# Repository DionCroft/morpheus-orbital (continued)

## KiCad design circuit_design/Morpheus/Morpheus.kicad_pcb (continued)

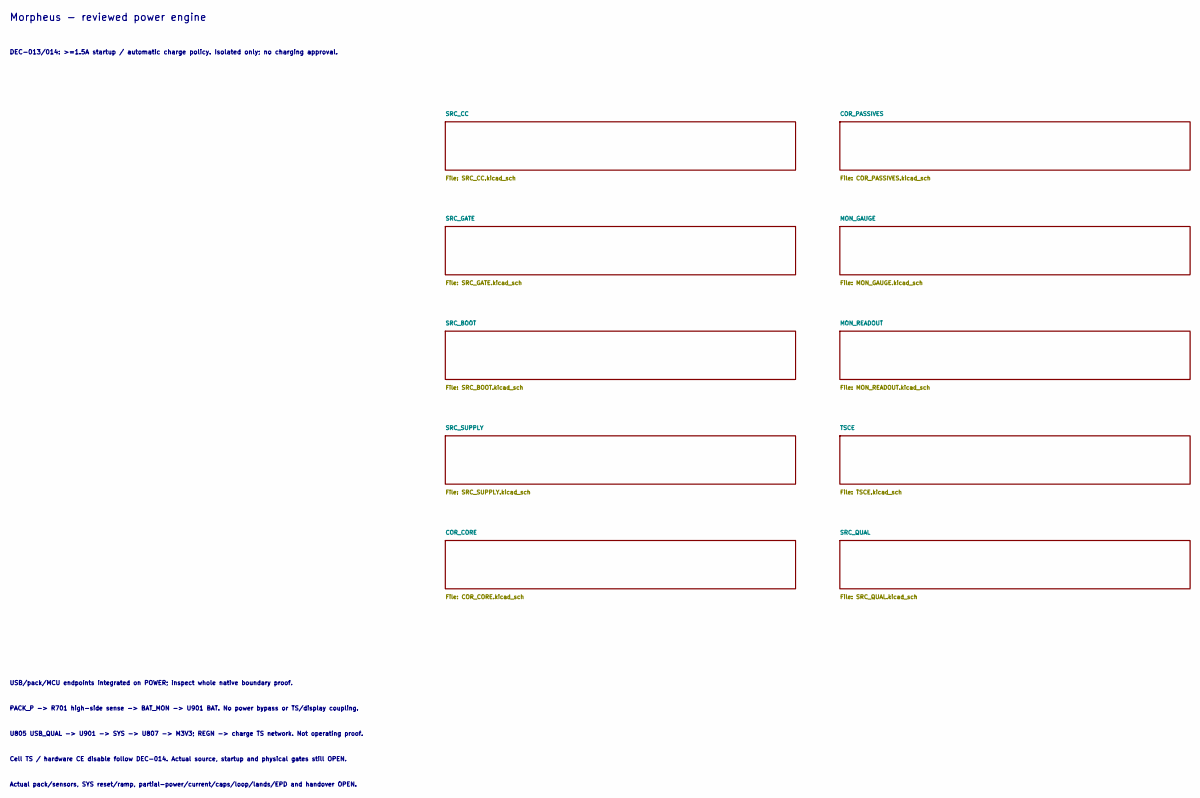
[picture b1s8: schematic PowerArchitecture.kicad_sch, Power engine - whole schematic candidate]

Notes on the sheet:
Morpheus - reviewed power engine
DEC-013/014: >=1.5A startup / automatic charge policy. Isolated only; no charging approval.
USB/pack/MCU endpoints integrated on POWER; inspect whole native boundary proof.
PACK_P -> R701 high-side sense -> BAT_MON -> U901 BAT. No power bypass or TS/display coupling.
U805 USB_QUAL -> U901 -> SYS -> U807 -> M3V3; REGN -> charge TS network. Not operating proof.
Cell TS / hardware CE disable follow DEC-014. Actual source, startup and physical gates still OPEN.
Actual pack/sensors, SYS reset/ramp, partial-power/current/caps/loop/lands/EPD and handover OPEN.

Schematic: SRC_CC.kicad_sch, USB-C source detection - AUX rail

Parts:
C801: 1u/50V; Samsung_C0805; ManufacturerPartNumber CL21B105KBFNNNE
C802: 4.7u/50V; Samsung_C1206; ManufacturerPartNumber CL31B475KBHNNNE
C803: 100n/50V; Samsung_C0603; ManufacturerPartNumber CL10B104KB8NNNC
R801: 0R - direct VBUS sense; R_0603_1608Metric; ManufacturerPartNumber RC0603JR-070RL
R802: 10k 1%; R_0603_1608Metric; ManufacturerPartNumber RC0603FR-0710KL
R812: 220R 1% 0.25W 1206; R_1206_3216Metric; ManufacturerPartNumber RC1206FR-07220RL
U801: TPS70933DBVR - AUX; TI_DBV0005A; ManufacturerPartNumber TPS70933DBVR
U802: FUSB303B - GPIO sink; Onsemi_722AG; ManufacturerPartNumber FUSB303BTMX

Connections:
C_ADVERT_N: R802.2, U802.7 (OUT1_ADVERT_N); also elsewhere on the board
C_AUDIO_OK: U802.6 (OUT3_AUDIO_N); also elsewhere on the board
C_AUX_IN: C801.1, R812.2, U801.1 (IN)
C_CC1: U802.1 (CC1); also elsewhere on the board
C_CC2: U802.2 (CC2); also elsewhere on the board
C_CC3V3: C802.1, C803.1, R802.1, U801.5 (OUT), U802.12 (VDD); also elsewhere on the board
C_PORT_DEBUG_N: U802.3 (PORT_DEBUG_N); also elsewhere on the board
C_SINK_OK: U802.9 (ID_SINK_OK); also elsewhere on the board
C_USB_RAW: R801.1, R812.1; also elsewhere on the board
C_VB_SENSE: R801.2, U802.4 (VBUS_DET)
GND: C801.2, C802.2, C803.2, U801.2 (GND), U802.10 (GND), U802.11 (EN_N); also elsewhere on the board

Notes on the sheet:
USB-C source detection - AUX rail
ISOLATED FUNCTIONAL CANDIDATE - primary conditions / actual integration / physical gates OPEN
FUSB PORT has10k sink strap, then DEBUG_N output; ADDR open selects GPIO.
R8010R connects FUSB VBUS_DET directly; old TUSB900k divider is NOT compatible.
R812220R limits AUX branch under stated5.5V/R/temperature conditions. Startup/lands OPEN.

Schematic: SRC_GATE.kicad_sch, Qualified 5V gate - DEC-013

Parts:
C804, C805: 100n/50V; Samsung_C0603; ManufacturerPartNumber CL10B104KB8NNNC
C806: 1u/50V; Samsung_C0805; ManufacturerPartNumber CL21B105KBFNNNE
C807: 10u/50V; Samsung_C1210; ManufacturerPartNumber CL32B106KBJNNNE
C816: 220n/50V; Samsung_C0805; ManufacturerPartNumber CL21B224KBFNNNE
R804: 300k 1%; R_0603_1608Metric; ManufacturerPartNumber RC0603FR-07300KL
R805: 249k 1%; R_0603_1608Metric; ManufacturerPartNumber RC0603FR-07249KL
R806: 22k 1%; R_0603_1608Metric; ManufacturerPartNumber RC0603FR-0722KL
U803: SN74LVC1G14DBVR; TI_DBV0005A; ManufacturerPartNumber SN74LVC1G14DBVR
U804: TPS389030DSET; TI_DSE0006A; ManufacturerPartNumber TPS389030DSET
U805: TPS2553DBVR; TI_DBV0006A; ManufacturerPartNumber TPS2553DBVR

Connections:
C_ADVERT_N: U803.2 (A); also elsewhere on the board
C_ADVERT_OK: U803.4 (Y); also elsewhere on the board
C_CC3V3: C804.1, C805.1, U803.5 (VCC), U804.1 (SENSE), U804.3 (MR_N), U804.4 (VDD); also elsewhere on the board
C_CC_CT: C816.1, U804.5 (CT)
C_DRV: R804.1; also elsewhere on the board
C_SRC_ILIM: R806.1, U805.5 (ILIM)
C_SW_ENABLE: R804.2, R805.1, U804.6 (RESET_N), U805.3 (EN)
C_USB_QUAL: C807.1, U805.6 (OUT); also elsewhere on the board
C_USB_RAW: C806.1, U805.1 (IN); also elsewhere on the board
GND: C804.2, C805.2, C806.2, C807.2, C816.2, R805.2, R806.2, U803.3 (GND), U804.2 (GND), U805.2 (GND); also elsewhere on the board

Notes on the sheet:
Qualified 5V gate - DEC-013
ISOLATED FUNCTIONAL CANDIDATE - primary conditions / actual integration / physical gates OPEN
TPS3890 RESET6 clamps EN; MR3 tied VDD4. Numerical map is NOT TPS3808-compatible.
R80622k + separate AUX220R: conditional DC budget only; ramp/transient/compliance OPEN.
C816220nF CT5-to-GND gives nominal235ms only; effectiveC/leakage/dynamic proof held.

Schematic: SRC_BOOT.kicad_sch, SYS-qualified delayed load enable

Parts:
C808, C811: 100n/50V; Samsung_C0603; ManufacturerPartNumber CL10B104KB8NNNC
C809, C810: 10u/50V; Samsung_C1210; ManufacturerPartNumber CL32B106KBJNNNE
C817: 220n/50V; Samsung_C0805; ManufacturerPartNumber CL21B224KBFNNNE
R808: 470k 1%; R_0603_1608Metric; ManufacturerPartNumber RC0603FR-07470KL
R809: 1M 1%; R_0603_1608Metric; ManufacturerPartNumber RC0603FR-071ML
U806: TPS389030DSET; TI_DSE0006A; ManufacturerPartNumber TPS389030DSET
U807: TPS63020DSJR; TI_DSJ14_PAD; ManufacturerPartNumber TPS63020DSJR

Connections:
3V3: U807.4 (VOUT4), U807.5 (VOUT5); also elsewhere on the board
C_BOOT_EN: R808.2, R809.1, U806.6 (RESET_N), U807.12 (EN)
C_FB: U807.3 (FB); also elsewhere on the board
C_L1: U807.8 (L1_8), U807.9 (L1_9); also elsewhere on the board
C_L2: U807.6 (L2_6), U807.7 (L2_7); also elsewhere on the board
C_SYS: C808.1, C809.1, C810.1, C811.1, R808.1, U806.1 (SENSE), U806.3 (MR_N), U806.4 (VDD), U807.1 (VINA), U807.10 (VIN10), U807.11 (VIN11); also elsewhere on the board
C_SYS_CT: C817.1, U806.5 (CT)
GND: C808.2, C809.2, C810.2, C811.2, C817.2, R809.2, U806.2 (GND), U807.2 (GND), U807.13 (PS_SYNC), U807.PAD (PGND_PAD_SWID); also elsewhere on the board

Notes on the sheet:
SYS-qualified delayed load enable
ISOLATED FUNCTIONAL CANDIDATE - primary conditions / actual integration / physical gates OPEN
TPS389030 rising2.907V nominal; R808470k bounds RESET load. CT220nF delay is nominal only.
U806 RESET6/MR3/VDD4/SENSE1; TPS63020 UVLO covers below POR. Actual load/transients OPEN.
PAD is an explicitly software-only thermal identifier. PS LOW enables low-load power save.

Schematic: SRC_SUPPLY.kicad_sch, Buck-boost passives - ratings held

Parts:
C812, C813, C814: 22u/25V; Samsung_C1210; ManufacturerPartNumber CL32B226KAJNNNE
L801: 1.5uH - current / lands HELD; Coilcraft_XGL4020; ManufacturerPartNumber XGL4020-152MEC
R810: 1M 0.1%; R_0603_1608Metric; ManufacturerPartNumber RT0603BRD071ML
R811: 180k 0.1%; Panasonic_ERA3A; ManufacturerPartNumber ERA3AEB184V

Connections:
3V3: C812.1, C813.1, C814.1, R810.1; also elsewhere on the board
C_FB: R810.2, R811.1; also elsewhere on the board
C_L1: L801.1; also elsewhere on the board
C_L2: L801.2; also elsewhere on the board
GND: C812.2, C813.2, C814.2, R811.2; also elsewhere on the board

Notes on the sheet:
Buck-boost passives - ratings held
ISOLATED FUNCTIONAL CANDIDATE - primary conditions / actual integration / physical gates OPEN
L8011.5uH +3x22uF follows documented nominal matrix; effective capacitance/inductor current still OPEN.
TI p15:1M/180k0.1% sets3.278V nominal; ripple/thermal/PCB gates OPEN.
Steady bounds include FB/PFM/line/load; they are NOT startup/load-step/fault guarantees.

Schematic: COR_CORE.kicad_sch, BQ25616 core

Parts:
U901: BQ25616RTWR NON-J; TI_RTW24_PAD; ManufacturerPartNumber BQ25616RTWR

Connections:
C_AGND: U901.6 (OTG); also elsewhere on the board
C_BAT_MON: U901.13 (BAT13), U901.14 (BAT14); also elsewhere on the board
C_BTST: U901.21 (BTST); also elsewhere on the board
C_CE9_N: U901.9 (CE_N); also elsewhere on the board
C_ICHG: U901.10 (ICHG); also elsewhere on the board
C_ILIM: U901.8 (ILIM); also elsewhere on the board
C_PG_N: U901.7 (PG_N); also elsewhere on the board
C_PMID: U901.23 (PMID); also elsewhere on the board
C_REGN: U901.22 (REGN); also elsewhere on the board
C_STAT_N: U901.5 (STAT_N); also elsewhere on the board
C_SW: U901.19 (SW19), U901.20 (SW20); also elsewhere on the board
C_SYS: U901.15 (SYS15), U901.16 (SYS16); also elsewhere on the board
C_TS11: U901.11 (TS); also elsewhere on the board
C_USB_QUAL: U901.1 (VAC), U901.24 (VBUS); also elsewhere on the board
C_VSET: U901.12 (VSET); also elsewhere on the board
GND: U901.17 (GND17), U901.18 (GND18), U901.PAD (PGND_SWID); also elsewhere on the board

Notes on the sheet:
BQ25616 non-J power-path functions
FUNCTIONAL CANDIDATE ONLY - source / permission / actual cell / lands / operating gates OPEN
VAC1=VBUS24, ACDRV2 open: manufacturer no-external-OVP option, NOT surge immunity.
BAT13/14 both charge and discharge through internal BATFET. SYS15/16 is NOT5V.
BTST21 consumes bootstrap supply; PMID23 supplies switching stage; SW19/20 drives L901.
D+3/D-4 NC: no charger loading on ESP32 USB. OTG6 LOW prevents intentional boost mode.
CE9/TS11 connect TSCE: autonomous cell sensing / manual disable; source and physical gates OPEN.
PAD is an unnumbered manufacturer thermal contact using an explicit software identifier.

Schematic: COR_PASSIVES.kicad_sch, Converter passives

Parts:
C90: 1n/50V C0G; Murata_GRM155_1nF_C0G_0402; ManufacturerPartNumber GRM1555C1H102JA01D
C901: 1u/50V; Samsung_C0805; ManufacturerPartNumber CL21B105KBFNNNE
C902, C905, C906, C907, C908: 10u/50V; Samsung_C1210; ManufacturerPartNumber CL32B106KBJNNNE
C903: 4.7u/50V; Samsung_C1206; ManufacturerPartNumber CL31B475KBHNNNE
C904: 47n/50V; Samsung_C0603; ManufacturerPartNumber CL10B473KB8NNNC
L901: 1uH - ratings / lands OPEN; Coilcraft_XAL5030; ManufacturerPartNumber XAL5030-102MEC
NT901: AGND STAR; AGND_Star_Thermal
R901: 1.5k 1% - ICHG; R_0603_1608Metric; ManufacturerPartNumber RC0603FR-071K5L
R902: 10k 1% - VSET; R_0603_1608Metric; ManufacturerPartNumber RC0603FR-0710KL
R903: 510R 1% - ILIM; R_0603_1608Metric; ManufacturerPartNumber RC0603FR-07510RL

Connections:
C_AGND: C903.2, NT901.1, R901.2, R902.2, R903.2; also elsewhere on the board
C_BAT_MON: C905.1; also elsewhere on the board
C_BTST: C904.1; also elsewhere on the board
C_ICHG: R901.1; also elsewhere on the board
C_ILIM: R903.1; also elsewhere on the board
C_PMID: C90.1, C902.1; also elsewhere on the board
C_REGN: C903.1; also elsewhere on the board
C_SW: C904.2, L901.1; also elsewhere on the board
C_SYS: C906.1, C907.1, C908.1, L901.2; also elsewhere on the board
C_USB_QUAL: C901.1; also elsewhere on the board
C_VSET: R902.1; also elsewhere on the board
GND: C90.2, C901.2, C902.2, C905.2, C906.2, C907.2, C908.2, NT901.2; also elsewhere on the board

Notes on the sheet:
Converter passives - effective C / current held
FUNCTIONAL CANDIDATE ONLY - source / permission / actual cell / lands / operating gates OPEN
C904 spans BTST-SW, never BTST-GND. L901 spans SW-SYS, not BAT-SYS.
Three nominal10uF SYS parts do NOT prove effectiveC>10uF / loop / ripple / thermal.
R9011.5k: conditional639..715/R at primary rows; actual cell/current acceptance OPEN.
R90210k selects4.1V non-J; R903510R only unknown-source ILIM, NOT universal clamp.
Exact MPNs/lands reviewed; effective C, dynamic current and assembly qualification remain held.

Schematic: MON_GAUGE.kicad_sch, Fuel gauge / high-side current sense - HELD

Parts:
C701: 1u/50V; Samsung_C0805; ManufacturerPartNumber CL21B105KBFNNNE
C702: 470n/50V; Samsung_C0805; ManufacturerPartNumber CL21B474KBFNNNE
R701: 10m 1% 1W 50ppm/K; Bourns_CRF1206; ManufacturerPartNumber CRF1206-FZ-R010ELF
R702, R703: 10k 1%; R_0603_1608Metric; ManufacturerPartNumber RC0603FR-0710KL
R704, R705: 1M 1%; R_0603_1608Metric; ManufacturerPartNumber RC0603FR-071ML
U701: BQ27441DRZR-G1A; TI_DRZ0012A; ManufacturerPartNumber BQ27441DRZR-G1A

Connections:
3V3: R703.1; also elsewhere on the board
C_BAT_MON: R701.2, U701.7 (SRN); also elsewhere on the board
C_BIN: R702.1, U701.10 (BIN)
C_GAUGE1V8: C702.1, U701.5 (VDD_1V8)
C_PACK_P: C701.1, R701.1, U701.6 (BAT_KELVIN), U701.8 (SRP); also elsewhere on the board
FUEL_GAUGE_INT: R703.2, U701.12 (GPOUT); also elsewhere on the board
GND: C701.2, C702.2, R702.2, R704.2, R705.2, U701.3 (VSS), U701.13 (PWPD_FIG6); also elsewhere on the board
I2C_SCL: R705.1, U701.2 (SCL); also elsewhere on the board
I2C_SDA: R704.1, U701.1 (SDA); also elsewhere on the board

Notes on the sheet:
Morpheus - Fuel gauge / high-side current sense - HELD
INTEGRATED FUNCTION CANDIDATE - reset/current/physical qualification OPEN; no charge release
PACK_P is Kelvin cell-positive; BAT_MON connects only after high-side sense.
BIN10k = embedded policy, NOT removable-pack detection. No external rail on BIN/VDD.
PWPD13 follows TI Fig6, not numbered I/O. Primary lands reviewed; assembly remains held.
No gauge LDO load except decoupling. Chemistry/reset/I2C partial-power/current gates OPEN.

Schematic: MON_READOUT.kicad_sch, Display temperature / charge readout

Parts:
C703, C704: 100n/50V; Samsung_C0603; ManufacturerPartNumber CL10B104KB8NNNC
J702: Display NTC - lands HELD; Harwin_M20-9990246; ManufacturerPartNumber M20-9990246
R706, R708, R709: 10k 1%; R_0603_1608Metric; ManufacturerPartNumber RC0603FR-0710KL
R707: 1k 1%; R_0603_1608Metric; ManufacturerPartNumber RC0603FR-071KL
R710, R711: 2.2k 1%; R_0603_1608Metric; ManufacturerPartNumber RC0603FR-072K2L
TH702: B57861S0103F040 OFFBOARD
U702: ADS1115IDGSR; TI_DGS0010A; ManufacturerPartNumber ADS1115IDGSR

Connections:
3V3: C703.1, R706.1, R708.1, R709.1, R710.1, R711.1, U702.5 (AIN1), U702.8 (VDD); also elsewhere on the board
C_PG_N: R709.2, U702.7 (AIN3); also elsewhere on the board
C_STAT_N: R708.2, U702.6 (AIN2); also elsewhere on the board
C_TEMP_FILT: C704.1, R707.2, U702.4 (AIN0)
C_TEMP_RAW: J702.1 (NTC), R706.2, R707.1, TH702.1
GND: C703.2, C704.2, J702.2 (GND), TH702.2, U702.1 (ADDR), U702.3 (GND); also elsewhere on the board
I2C_SCL: R711.2, U702.10 (SCL); also elsewhere on the board
I2C_SDA: R710.2, U702.9 (SDA); also elsewhere on the board

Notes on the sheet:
Morpheus - Display NTC / charge status - DRAFT
INTEGRATED FUNCTION CANDIDATE - reset/current/physical qualification OPEN; no charge release
ADDR=GND ->0x48; AIN0=filtered display NTC; AIN1=M3V3 reference.
AIN2=STAT_N and AIN3=PG_N. No electrical connection to charger TS.
One2.2k pair only. I2C<=100kHz; gauge bus-free>=66us. Cb<=100pF; tr/tf<=300ns.
FSR4.096V / slow sampling / loading / thermal attachment / error policy require qualification.

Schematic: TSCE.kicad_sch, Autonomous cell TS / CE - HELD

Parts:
J602: Cell NTC header - lands HELD; Harwin_M20-9990246; ManufacturerPartNumber M20-9990246
J603: Disable charge jumper - HELD; Harwin_M20-9990246; ManufacturerPartNumber M20-9990246
R601: 5.9k 1%; R_0603_1608Metric; ManufacturerPartNumber RC0603FR-075K9L
R602: 46.4k 1%; R_0603_1608Metric; ManufacturerPartNumber RC0603FR-0746K4L
R605: 10k 1%; R_0603_1608Metric; ManufacturerPartNumber RC0603FR-0710KL
TH601: B57861S0103F040 - OFFBOARD

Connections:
C_AGND: J602.2 (RETURN), R602.2, R605.1, TH601.2; also elsewhere on the board
C_CE9_N: J603.1 (CE_DISABLE), R605.2; also elsewhere on the board
C_REGN: J603.2 (REGN), R601.1; also elsewhere on the board
C_TS11: J602.1 (CELL_NTC), R601.2, R602.1, TH601.1; also elsewhere on the board

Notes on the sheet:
Morpheus - autonomous cell temperature / charge disable
INTEGRATED FUNCTION REVIEW ONLY - converter/source/readout joined; qualification OPEN
DEC-014 automatic policy: source and actual cell NTC still require qualification. No charging approval.
CELL TEMPERATURE
HARDWARE CHARGE DISABLE
SOURCE / PHYSICAL GATES OPEN
J603 open: automatic policy. Closed: CE tied to REGN for disable; analog/startup gates OPEN.
J602 is a separate two-wire CELL-ATTACHED sensor; not an invented third battery lead.
Actual cell attachment, CE leakage/startup, source qualification and physical margins remain OPEN.

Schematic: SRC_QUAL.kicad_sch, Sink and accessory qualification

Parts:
C1601, C1602, C1603: 100n/50V; Samsung_C0603; ManufacturerPartNumber CL10B104KB8NNNC
R813, R814, R815: 10k 1%; R_0603_1608Metric; ManufacturerPartNumber RC0603FR-0710KL
U1601, U1602: SN74LVC1G14DBVR; TI_DBV0005A; ManufacturerPartNumber SN74LVC1G14DBVR
U1603: SN74HCS08PW; TI_PW0014A; ManufacturerPartNumber SN74HCS08PWR

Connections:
C_ACCESSORY_OK: U1603.6 (2Y), U1603.10 (3B)
C_ADVERT_OK: U1603.1 (1A); also elsewhere on the board
C_ADVERT_SINK: U1603.3 (1Y), U1603.9 (3A)
C_AUDIO_OK: R815.2, U1603.4 (2A); also elsewhere on the board
C_CC3V3: C1601.1, C1602.1, C1603.1, R814.1, R815.1, U1601.5 (VCC), U1602.5 (VCC), U1603.14 (VCC); also elsewhere on the board
C_DEBUG_INV: U1601.4 (Y), U1602.2 (A)
C_DEBUG_OK: U1602.4 (Y), U1603.5 (2B)
C_DRV: U1603.8 (3Y); also elsewhere on the board
C_PORT_DEBUG_N: R813.1, U1601.2 (A); also elsewhere on the board
C_SINK_OK: R814.2, U1603.2 (1B); also elsewhere on the board
GND: C1601.2, C1602.2, C1603.2, R813.2, U1601.3 (GND), U1602.3 (GND), U1603.7 (GND), U1603.12 (4A), U1603.13 (4B); also elsewhere on the board

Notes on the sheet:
USB-C qualification - sink, >=1.5A, no audio/debug accessory
R813 must allow strap LOW first and push-pull DEBUG HIGH later; no hard-ground shortcut.
1Y=ADVERT_OK AND SINK_OK; 2Y=AUDIO_OK AND DEBUG_OK; 3Y drives R804. Unused4A/4B grounded.
10k strap trades standby current for receiver leakage margin. Settled DC only; not a universal ramp proof.
FUSB tEN100ms is I2C access, NOT a GPIO-ready timer. CT nominal delay is not a readiness guarantee.
MPNs/lands reviewed; partial-power, transients, source withdrawal and assembly remain held.

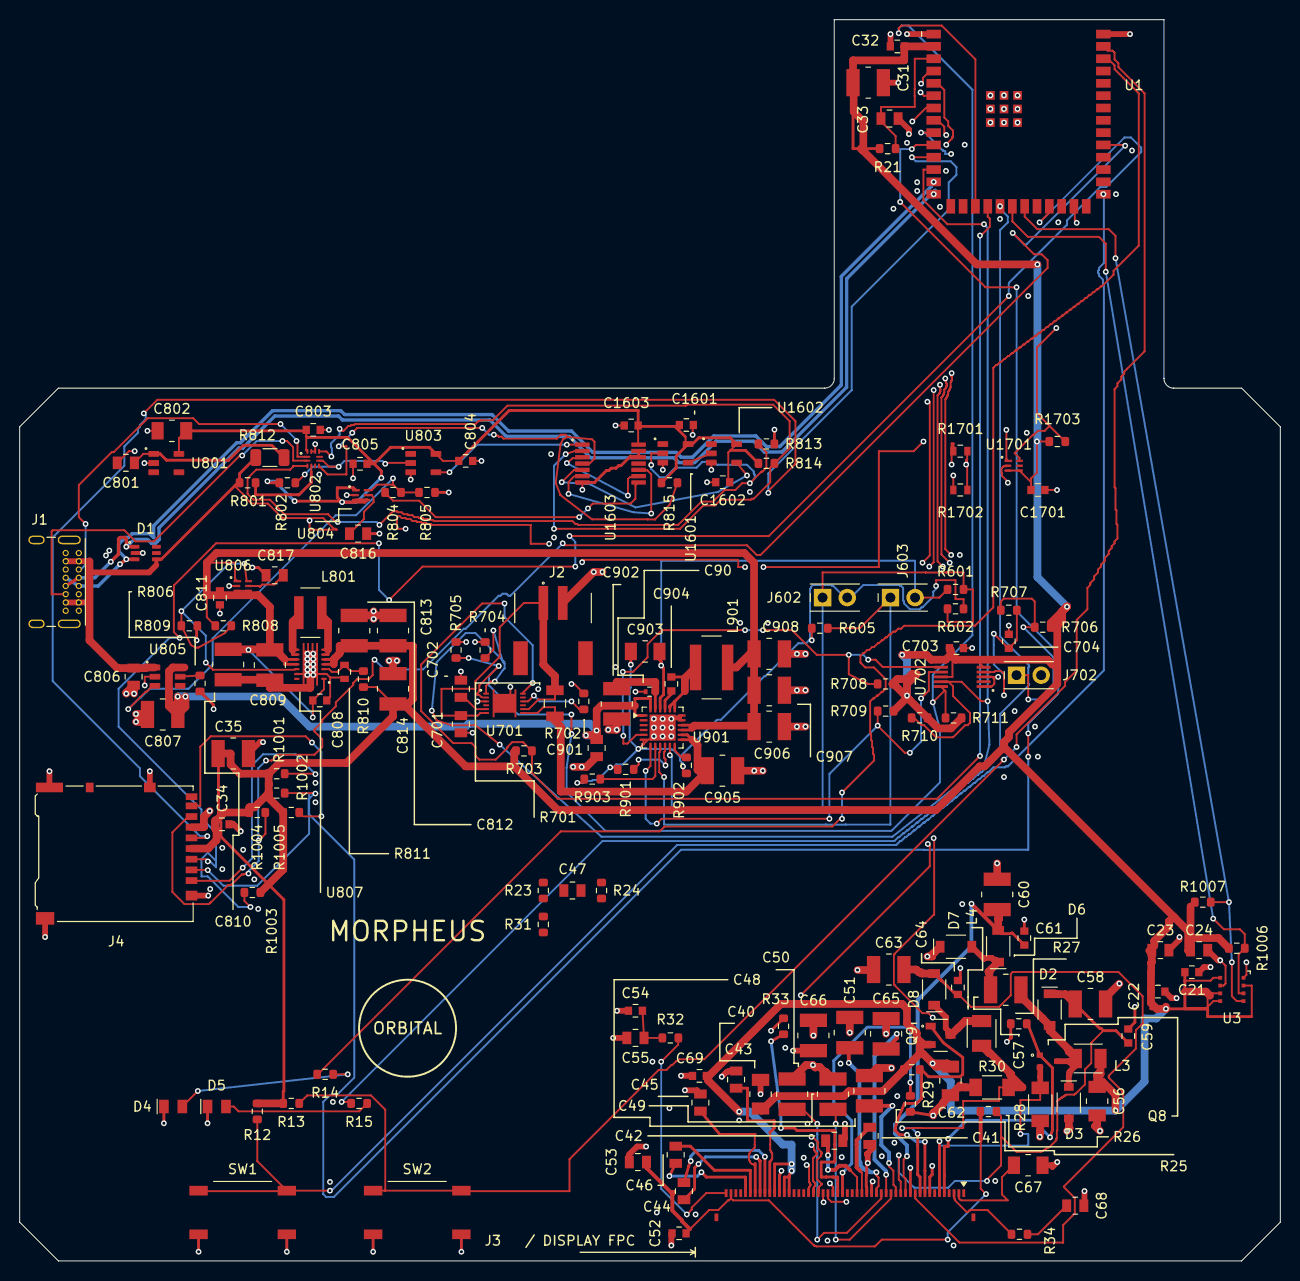
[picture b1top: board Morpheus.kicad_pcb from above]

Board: 6 copper layers, 130.0 x 128.0 mm, 169 parts (0 on the bottom side), 106 nets.

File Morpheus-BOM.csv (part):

"References","Quantity","Value","Manufacturer","ManufacturerPartNumber","LCSC","Footprint","Datasheet","DNP","ExcludeFromBoard","ExcludeFromBOM","CandidateScope"
"C21","1","100nF","Samsung Electro-Mechanics","CL10B104KB8NNNC","","Morpheus_Power_Reviewed:Samsung_C0603","https://product.samsungsem.com/mlcc/CL10B104KB8NNN.do","","","","EXACT_PRIMARY_NOMINAL_PRESERVED; EFFECTIVE_C_LOOP_ASSEMBLY_QUALIFICATION_HELD"
"C22","1","100nF","Samsung Electro-Mechanics","CL10B104KB8NNNC","","Morpheus_Power_Reviewed:Samsung_C0603","https://product.samsungsem.com/mlcc/CL10B104KB8NNN.do","","","","EXACT_PRIMARY_NOMINAL_PRESERVED; EFFECTIVE_C_LOOP_ASSEMBLY_QUALIFICATION_HELD"
"C23","1","1uF","Samsung Electro-Mechanics","CL21B105KBFNNNE","","Morpheus_Power_Reviewed:Samsung_C0805","https://product.samsungsem.com/mlcc/CL21B105KBFNNN.do","","","","EXACT_PRIMARY_NOMINAL_PRESERVED; EFFECTIVE_C_LOOP_ASSEMBLY_QUALIFICATION_HELD"
"C24","1","1uF","Samsung Electro-Mechanics","CL21B105KBFNNNE","","Morpheus_Power_Reviewed:Samsung_C0805","https://product.samsungsem.com/mlcc/CL21B105KBFNNN.do","","","","EXACT_PRIMARY_NOMINAL_PRESERVED; EFFECTIVE_C_LOOP_ASSEMBLY_QUALIFICATION_HELD"
"C31","1","10uF","Samsung Electro-Mechanics","CL32B106KBJNNNE","C138687","Morpheus_Power_Reviewed:Samsung_C1210","https://product.samsungsem.com/mlcc/CL32B106KBJNNN.do","","","","EXACT_PRIMARY_NOMINAL_PRESERVED; EFFECTIVE_C_LOOP_ASSEMBLY_QUALIFICATION_HELD"
"C32","1","100nF","Samsung Electro-Mechanics","CL10B104KB8NNNC","","Morpheus_Power_Reviewed:Samsung_C0603","https://product.samsungsem.com/mlcc/CL10B104KB8NNN.do","","","","EXACT_PRIMARY_NOMINAL_PRESERVED; EFFECTIVE_C_LOOP_ASSEMBLY_QUALIFICATION_HELD"
"C33","1","1uF","Samsung Electro-Mechanics","CL21B105KBFNNNE","","Morpheus_Power_Reviewed:Samsung_C0805","https://product.samsungsem.com/mlcc/CL21B105KBFNNN.do","","","","EXACT_PRIMARY_NOMINAL_PRESERVED; EFFECTIVE_C_LOOP_ASSEMBLY_QUALIFICATION_HELD"
"C34","1","100nF [ASSUMED local bypass]","Samsung Electro-Mechanics","CL10B104KB8NNNC","","Morpheus_Power_Reviewed:Samsung_C0603","https://product.samsungsem.com/mlcc/CL10B104KB8NNN.do","","","","EXACT_PRIMARY_NOMINAL_PRESERVED; EFFECTIVE_C_LOOP_ASSEMBLY_QUALIFICATION_HELD; PROVISIONAL_SD_LOCAL_DECOUPLING_ROLE_NOT_SOCKET_REQUIREMENT"
"C35","1","10uF [ASSUMED local bulk]","Samsung Electro-Mechanics","CL32B106KBJNNNE","C138687","Morpheus_Power_Reviewed:Samsung_C1210","https://product.samsungsem.com/mlcc/CL32B106KBJNNN.do","","","","EXACT_PRIMARY_NOMINAL_PRESERVED; EFFECTIVE_C_LOOP_ASSEMBLY_QUALIFICATION_HELD; PROVISIONAL_SD_LOCAL_DECOUPLING_ROLE_NOT_SOCKET_REQUIREMENT"
"C40","1","2.2uF/50V","Samsung Electro-Mechanics","CL31B225KBHNNNE","","Morpheus_Power_Reviewed:Samsung_C1206","https://product.samsungsem.com/mlcc/CL31B225KBHNNN.do","","","","EXACT_PRIMARY_NOMINAL_PRESERVED; EFFECTIVE_C_LOOP_ASSEMBLY_QUALIFICATION_HELD"
"C41","1","1uF/50V","Samsung Electro-Mechanics","CL21B105KBFNNNE","","Morpheus_Power_Reviewed:Samsung_C0805","https://product.samsungsem.com/mlcc/CL21B105KBFNNN.do","","","","EXACT_PRIMARY_NOMINAL_PRESERVED; EFFECTIVE_C_LOOP_ASSEMBLY_QUALIFICATION_HELD"
"C42","1","1uF/50V","Samsung Electro-Mechanics","CL21B105KBFNNNE","","Morpheus_Power_Reviewed:Samsung_C0805","https://product.samsungsem.com/mlcc/CL21B105KBFNNN.do","","","","EXACT_PRIMARY_NOMINAL_PRESERVED; EFFECTIVE_C_LOOP_ASSEMBLY_QUALIFICATION_HELD"
"C43","1","1uF/50V","Samsung Electro-Mechanics","CL21B105KBFNNNE","","Morpheus_Power_Reviewed:Samsung_C0805","https://product.samsungsem.com/mlcc/CL21B105KBFNNN.do","","","","EXACT_PRIMARY_NOMINAL_PRESERVED; EFFECTIVE_C_LOOP_ASSEMBLY_QUALIFICATION_HELD"
"C44","1","1uF/50V","Samsung Electro-Mechanics","CL21B105KBFNNNE","","Morpheus_Power_Reviewed:Samsung_C0805","https://product.samsungsem.com/mlcc/CL21B105KBFNNN.do","","","","EXACT_PRIMARY_NOMINAL_PRESERVED; EFFECTIVE_C_LOOP_ASSEMBLY_QUALIFICATION_HELD"
"C45","1","1uF/50V","Samsung Electro-Mechanics","CL21B105KBFNNNE","","Morpheus_Power_Reviewed:Samsung_C0805","https://product.samsungsem.com/mlcc/CL21B105KBFNNN.do","","","","EXACT_PRIMARY_NOMINAL_PRESERVED; EFFECTIVE_C_LOOP_ASSEMBLY_QUALIFICATION_HELD"
"C46","1","1uF/50V","Samsung Electro-Mechanics","CL21B105KBFNNNE","","Morpheus_Power_Reviewed:Samsung_C0805","https://product.samsungsem.com/mlcc/CL21B105KBFNNN.do","","","","EXACT_PRIMARY_NOMINAL_PRESERVED; EFFECTIVE_C_LOOP_ASSEMBLY_QUALIFICATION_HELD"
"C47","1","1uF/50V DNP","Samsung Electro-Mechanics","CL21B105KBFNNNE","","Morpheus_Power_Reviewed:Samsung_C0805","https://product.samsungsem.com/mlcc/CL21B105KBFNNN.do","DNP","","","EXACT_PRIMARY_NOMINAL_PRESERVED; EFFECTIVE_C_LOOP_ASSEMBLY_QUALIFICATION_HELD"
"C48","1","10uF/50V","Samsung Electro-Mechanics","CL32B106KBJNNNE","C138687","Morpheus_Power_Reviewed:Samsung_C1210","https://product.samsungsem.com/mlcc/CL32B106KBJNNN.do","","","","EXACT_PRIMARY_NOMINAL_PRESERVED; EFFECTIVE_C_LOOP_ASSEMBLY_QUALIFICATION_HELD"
"C49","1","10uF/50V","Samsung Electro-Mechanics","CL32B106KBJNNNE","C138687","Morpheus_Power_Reviewed:Samsung_C1210","https://product.samsungsem.com/mlcc/CL32B106KBJNNN.do","","","","EXACT_PRIMARY_NOMINAL_PRESERVED; EFFECTIVE_C_LOOP_ASSEMBLY_QUALIFICATION_HELD"
"C50","1","10uF/50V","Samsung Electro-Mechanics","CL32B106KBJNNNE","C138687","Morpheus_Power_Reviewed:Samsung_C1210","https://product.samsungsem.com/mlcc/CL32B106KBJNNN.do","","","","EXACT_PRIMARY_NOMINAL_PRESERVED; EFFECTIVE_C_LOOP_ASSEMBLY_QUALIFICATION_HELD"
"C51","1","10uF/50V","Samsung Electro-Mechanics","CL32B106KBJNNNE","C138687","Morpheus_Power_Reviewed:Samsung_C1210","https://product.samsungsem.com/mlcc/CL32B106KBJNNN.do","","","","EXACT_PRIMARY_NOMINAL_PRESERVED; EFFECTIVE_C_LOOP_ASSEMBLY_QUALIFICATION_HELD"
"C52","1","100nF/50V","Samsung Electro-Mechanics","CL10B104KB8NNNC","","Morpheus_Power_Reviewed:Samsung_C0603","https://product.samsungsem.com/mlcc/CL10B104KB8NNN.do","","","","EXACT_PRIMARY_NOMINAL_PRESERVED; EFFECTIVE_C_LOOP_ASSEMBLY_QUALIFICATION_HELD"
"C53","1","1uF/50V","Samsung Electro-Mechanics","CL21B105KBFNNNE","","Morpheus_Power_Reviewed:Samsung_C0805","https://product.samsungsem.com/mlcc/CL21B105KBFNNN.do","","","","EXACT_PRIMARY_NOMINAL_PRESERVED; EFFECTIVE_C_LOOP_ASSEMBLY_QUALIFICATION_HELD"
"C54","1","100nF/50V","Samsung Electro-Mechanics","CL10B104KB8NNNC","","Morpheus_Power_Reviewed:Samsung_C0603","https://product.samsungsem.com/mlcc/CL10B104KB8NNN.do","","","","EXACT_PRIMARY_NOMINAL_PRESERVED; EFFECTIVE_C_LOOP_ASSEMBLY_QUALIFICATION_HELD"
"C55","1","470nF/50V","Samsung Electro-Mechanics","CL21B474KBFNNNE","","Morpheus_Power_Reviewed:Samsung_C0805","https://product.samsungsem.com/mlcc/CL21B474KBFNNN.do","","","","REFERENCE_NOMINAL0.47UF_VCOMBD; EXACT_PRIMARY_IDENTITY_QUALIFIED_LANDS; EFFECTIVE_C_LOOP_INRUSH_QUALIFICATION_HELD"
"C56","1","4.7uF/50V","Samsung Electro-Mechanics","CL31B475KBHNNNE","","Morpheus_Power_Reviewed:Samsung_C1206","https://product.samsungsem.com/mlcc/CL31B475KBHNNN.do","","","","EXACT_PRIMARY_NOMINAL_PRESERVED; EFFECTIVE_C_LOOP_ASSEMBLY_QUALIFICATION_HELD"
"C57","1","10uF/50V","Samsung Electro-Mechanics","CL32B106KBJNNNE","C138687","Morpheus_Power_Reviewed:Samsung_C1210","https://product.samsungsem.com/mlcc/CL32B106KBJNNN.do","","","","EXACT_PRIMARY_NOMINAL_PRESERVED; EFFECTIVE_C_LOOP_ASSEMBLY_QUALIFICATION_HELD"
"C58","1","10uF/50V","Samsung Electro-Mechanics","CL32B106KBJNNNE","C138687","Morpheus_Power_Reviewed:Samsung_C1210","https://product.samsungsem.com/mlcc/CL32B106KBJNNN.do","","","","EXACT_PRIMARY_NOMINAL_PRESERVED; EFFECTIVE_C_LOOP_ASSEMBLY_QUALIFICATION_HELD"
"C59","1","100nF/50V","Samsung Electro-Mechanics","CL10B104KB8NNNC","","Morpheus_Power_Reviewed:Samsung_C0603","https://product.samsungsem.com/mlcc/CL10B104KB8NNN.do","","","","EXACT_PRIMARY_NOMINAL_PRESERVED; EFFECTIVE_C_LOOP_ASSEMBLY_QUALIFICATION_HELD"
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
